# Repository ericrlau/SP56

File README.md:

# SP56
## A ZMK-Powered BLE Keyboard, Inspired By Lily58 & Sofle

> :warning: **This is a partially tested project.** Do not use to create your own copy unless you are willing to debug the hardware and/or firmware. 
## Flash bootloader
Bootloader is pre-loaded on assembled pcbs. If you source your own BLE module you will need to unlock the module and flash the bootloader using the Nordic nrf command line tool. 
```
$ nrfjprog --recover --log 
```
```
$ nrfjprog -f nrf52 --program firmware/bootloader/COBO_nrf52840_bootloader-0.3.2-184-g64ea299_s140_6.1.1.hex
```

------------------------------------
## Upload Firmware 

- See ZMK docs for instructions on setting up ZMK and custimizing firmware.  
	* https://zmkfirmware.dev/docs/user-setup/
	* https://zmkfirmware.dev/docs/customization 
- Default *.uf2 files are pre-loaded on assembled pcbs. If you sourced and assembled your own pcb, you can file deafult pre-built firmware here: 
	- https://github.com/ericrlau/COBO-zmk-config/releases

## PCB
- Source files for pcb are in this repo. They are split into three kicad projects:
	- SP56: main pcb, left and right combined. 
	- SP56_Bottom: Bottom cover PCB. Left and right use the same part so only one copy is created. 
	- SP56_Plate: Switch plate PCB. This must be 1.2mm pcb to allow Kaihl Choc V1 switches to snap in. Left and right use the same part so only one copy is created. 
	- NOTE: KiCad files are created with nightly KiCad 5.99 builds, they are not compatible with current stable release of KiCad 5.
- Bill of materials [BOM Link](https://raw.githack.com/ericrlau/SP56/working/PCB/SP56/bom/ibom.html)
## Build Guide For PCBA
[Build Guide Link](./Build_Guide.md)

## Images

#### Prototype Build

#### Main PCB

#### FR4 Plate

#### Bottom PCB

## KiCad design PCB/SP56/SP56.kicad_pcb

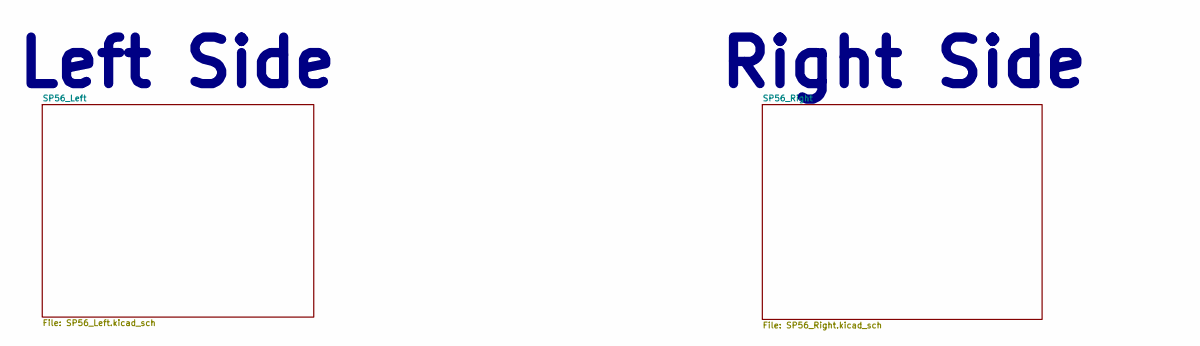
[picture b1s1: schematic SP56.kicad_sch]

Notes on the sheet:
Left Side
Right Side

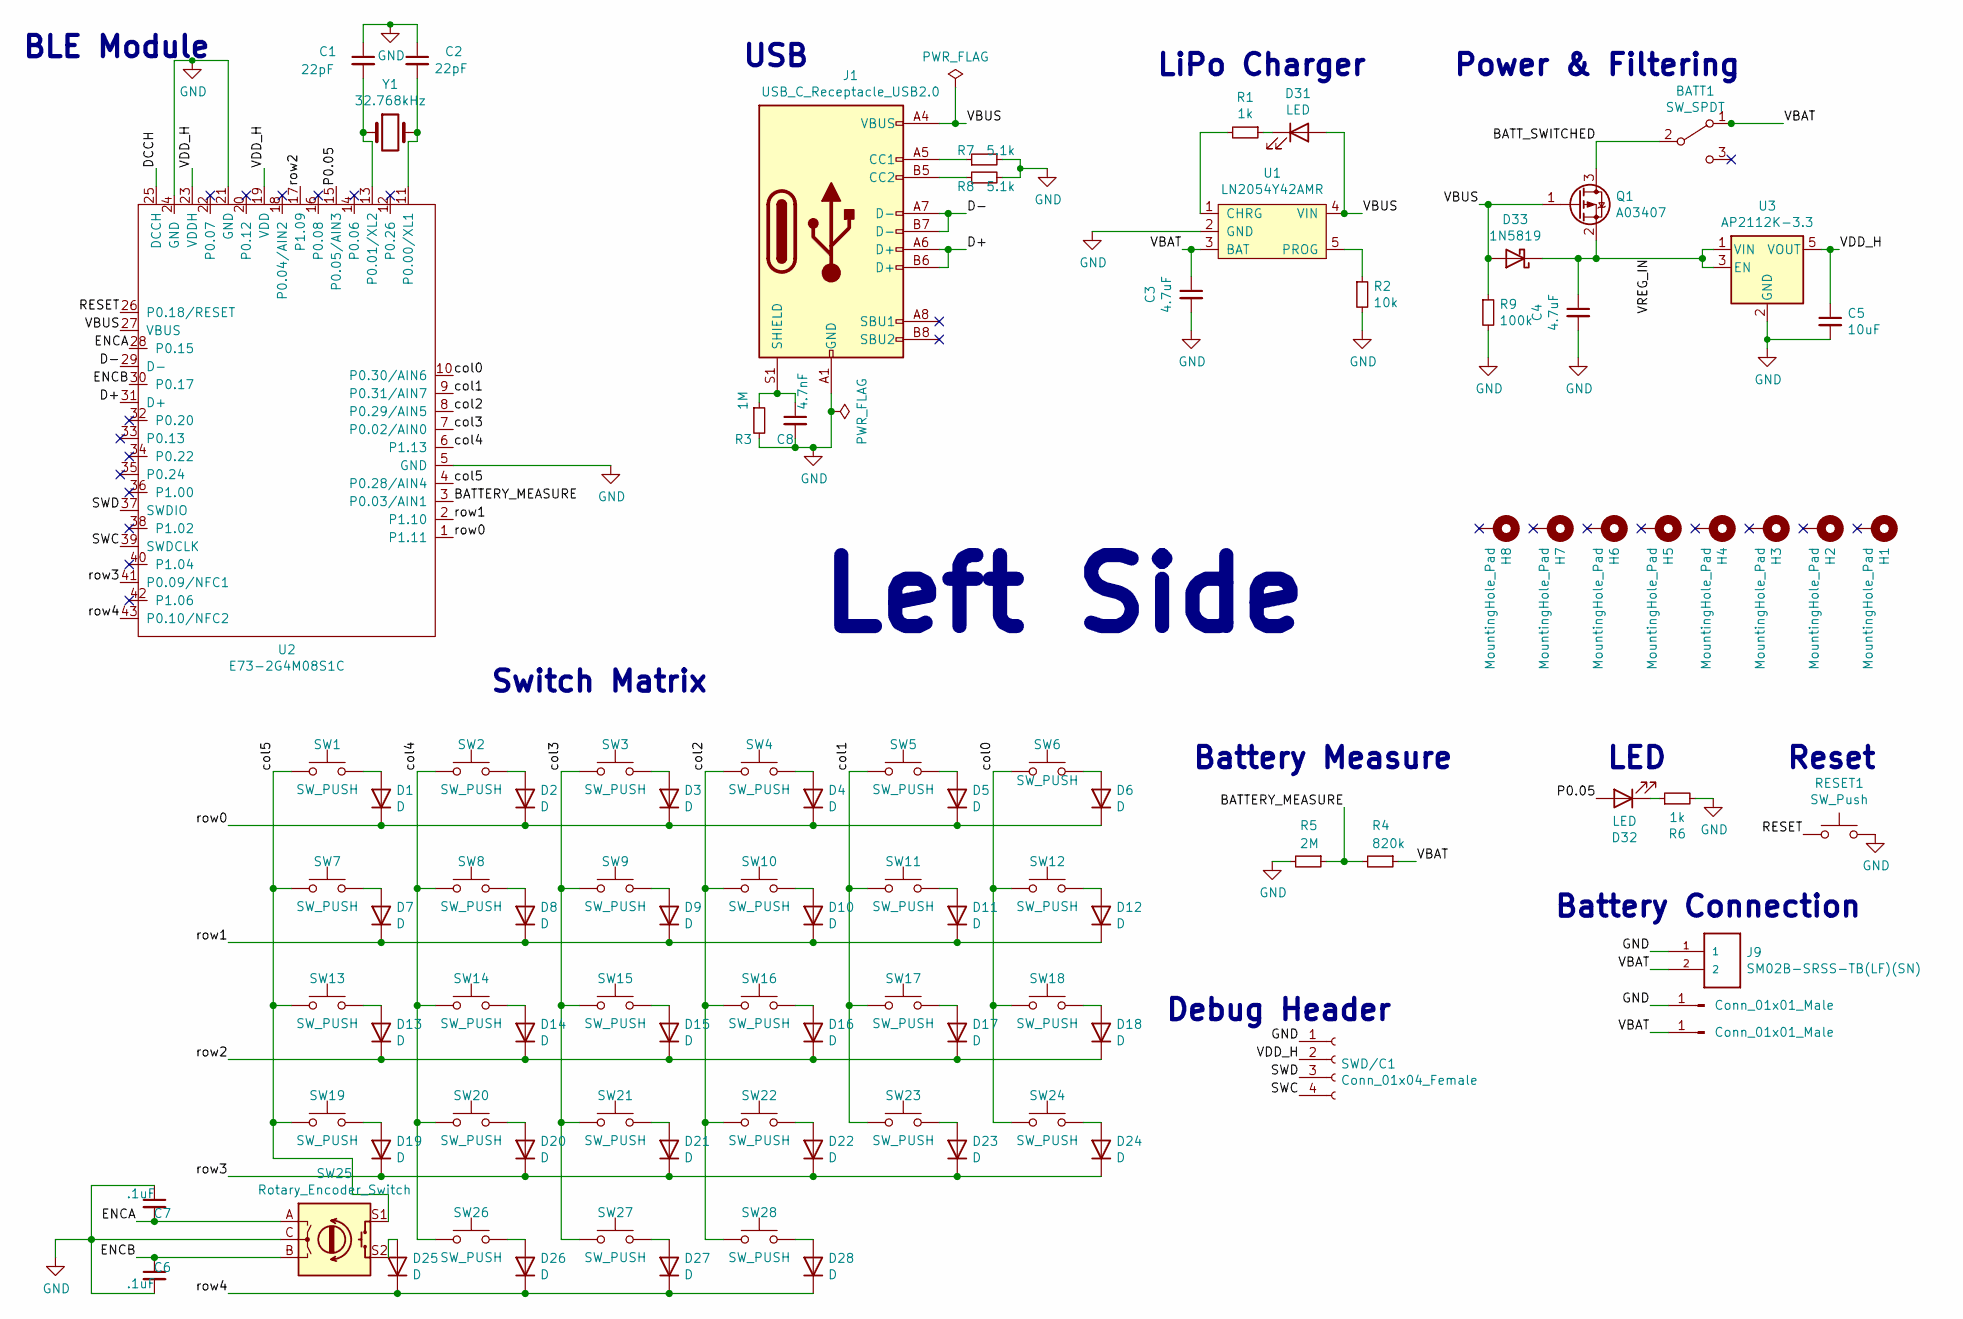
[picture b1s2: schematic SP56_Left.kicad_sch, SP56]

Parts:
BATT1: SW_SPDT; SW-TH_MSK12C02; LCSC_PN C431540
C1, C2: 22pF; C_0603_1608Metric; LCSC_PN C1653
C3, C4: 4.7uF; C_0603_1608Metric; LCSC_PN C19666
C5: 10uF; C_0603_1608Metric; LCSC_PN C87152
C6, C7: .1uF; C_0603_1608Metric
C8: 4.7nF; C_0603_1608Metric
D1, D2, D3, D4, D5, D6, D7, D8, D9, D10, D11, D12, D13, D14, D15, D16, D17, D18, D19, D20, D21, D22, D23, D24, D25, D26, D27, D28: D; D_SOD-123; LCSC_PN C402213
D31, D32: LED; LED_0603_1608Metric
D33: 1N5819; D_SOD-323_HandSoldering; LCSC_PN C489147
H1, H2, H3, H4, H5, H6, H7, H8: MountingHole_Pad; MountingHole_4.3mm_M4
J1: USB_C_Receptacle_USB2.0; USB-C_C168688; LCSC_PN C168688
J2, J3: Conn_01x01_Male; PinSocket_1x01_P1.27mm_Vertical
J9: SM02B-SRSS-TB(LF)(SN); LCSC_PN C160402
Q1: A03407; SOT-23; LCSC_PN C351408
R1, R6: 1k; R_0603_1608Metric; LCSC_PN C22548
R2: 10k; R_0603_1608Metric; LCSC_PN C98220
R3: 1M; R_0603_1608Metric
R4: 820k; R_0603_1608Metric; LCSC_PN C23252
R5: 2M; R_0603_1608Metric; LCSC_PN C177282
R7, R8: 5.1k; R_0603_1608Metric; LCSC_PN C105580
R9: 100k; R_0603_1608Metric; LCSC_PN C14675
RESET1: SW_Push; SW_SPST_B3U-1000P; LCSC_PN C231329
SW1, SW2, SW3, SW4, SW5, SW6, SW7, SW8, SW9, SW10, SW11, SW12, SW13, SW14, SW15, SW16, SW17, SW18, SW19, SW20, SW21, SW22, SW23, SW24, SW27, SW28: SW_PUSH; KailhLowProfile
SW25: Rotary_Encoder_Switch; RotaryEncoder_Alps_EC11E-Switch_Vertical_H20mm
SW26: SW_PUSH; KailhLowProfile_1.5U
SWD/C1: Conn_01x04_Female; PinHeader_1x04_P2.54mm_Vertical
U1: LN2054Y42AMR; SOT-23-5; LCSC_PN C141406
U2: E73-2G4M08S1C; E73-2G4M08S1C-52840_SMD; LCSC_PN C356849
U3: AP2112K-3.3; SOT-23-5; LCSC_PN C51118
Y1: 32.768kHz; Crystal_SMD_MicroCrystal_CM9V-T1A-2Pin_1.6x1.0mm; LCSC_PN C93230

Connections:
/SP56_Left/BATTERY_MEASURE: R4.2, R5.1, U2.3 (P0.03/AIN1)
/SP56_Left/BATT_SWITCHED: BATT1.2 (B), Q1.3 (D)
/SP56_Left/D+: J1.A6 (D+), J1.B6 (D+), U2.31 (D+)
/SP56_Left/D-: J1.A7 (D-), J1.B7 (D-), U2.29 (D-)
/SP56_Left/DCCH: U2.25 (DCCH)
/SP56_Left/ENCA: C7.2, SW25.A, U2.28 (P0.15)
/SP56_Left/ENCB: C6.1, SW25.B, U2.30 (P0.17)
/SP56_Left/P0.05: D32.2 (A), U2.15 (P0.05/AIN3)
/SP56_Left/RESET: RESET1.1, U2.26 (P0.18/RESET)
/SP56_Left/SWC: SWD/C1.4, U2.39 (SWDCLK)
/SP56_Left/SWD: SWD/C1.3, U2.37 (SWDIO)
/SP56_Left/VBAT: BATT1.1 (A), C3.1, J3.1, J9.2, R4.1, U1.3 (BAT)
/SP56_Left/VBUS: D31.2 (A), D33.2 (A), J1.A4 (VBUS), J1.A9 (VBUS), J1.B4 (VBUS), J1.B9 (VBUS), Q1.1 (G), R9.1, U1.4 (VIN), U2.27 (VBUS)
/SP56_Left/VDD_H: C5.1, SWD/C1.2, U2.19 (VDD), U2.23 (VDDH), U3.5 (VOUT)
/SP56_Left/VREG_IN: C4.1, D33.1 (K), Q1.2 (S), U3.1 (VIN), U3.3 (EN)
/SP56_Left/col0: SW6.1, SW12.1, SW18.1, SW24.1, U2.10 (P0.30/AIN6)
/SP56_Left/col1: SW5.1, SW11.1, SW17.1, SW23.1, U2.9 (P0.31/AIN7)
/SP56_Left/col2: SW4.1, SW10.1, SW16.1, SW22.1, SW28.1, U2.8 (P0.29/AIN5)
/SP56_Left/col3: SW3.1, SW9.1, SW15.1, SW21.1, SW27.1, U2.7 (P0.02/AIN0)
/SP56_Left/col4: SW2.1, SW8.1, SW14.1, SW20.1, SW26.1, U2.6 (P1.13)
/SP56_Left/col5: SW1.1, SW7.1, SW13.1, SW19.1, SW25.S1, U2.4 (P0.28/AIN4)
/SP56_Left/row0: D1.1 (K), D2.1 (K), D3.1 (K), D4.1 (K), D5.1 (K), D6.1 (K), U2.1 (P1.11)
/SP56_Left/row1: D7.1 (K), D8.1 (K), D9.1 (K), D10.1 (K), D11.1 (K), D12.1 (K), U2.2 (P1.10)
/SP56_Left/row2: D13.1 (K), D14.1 (K), D15.1 (K), D16.1 (K), D17.1 (K), D18.1 (K), U2.17 (P1.09)
/SP56_Left/row3: D19.1 (K), D20.1 (K), D21.1 (K), D22.1 (K), D23.1 (K), D24.1 (K), U2.41 (P0.09/NFC1)
/SP56_Left/row4: D25.1 (K), D26.1 (K), D27.1 (K), D28.1 (K), U2.43 (P0.10/NFC2)
GND: C1.1, C2.1, C3.2, C4.2, C5.2, C6.2, C7.1, C8.2, J1.A1 (GND), J1.A12 (GND), J1.B1 (GND), J1.B12 (GND), J2.1, J9.1, R2.2, R3.2, R5.2, R6.2, R7.2, R8.2, R9.2, RESET1.2, SW25.C, SWD/C1.1, U1.2 (GND), U2.5 (GND), U2.21 (GND), U2.24 (GND), U3.2 (GND); also elsewhere on the board
unnamed: C1.2, U2.13 (P0.01/XL2), Y1.1
unnamed: C2.2, U2.11 (P0.00/XL1), Y1.2
unnamed: C8.1, J1.S1 (SHIELD), R3.1
unnamed: D1.2 (A), SW1.2
unnamed: D2.2 (A), SW2.2
unnamed: D3.2 (A), SW3.2
unnamed: D4.2 (A), SW4.2
unnamed: D5.2 (A), SW5.2
unnamed: D6.2 (A), SW6.2
unnamed: D7.2 (A), SW7.2
unnamed: D8.2 (A), SW8.2
unnamed: D9.2 (A), SW9.2
unnamed: D10.2 (A), SW10.2
unnamed: D11.2 (A), SW11.2
unnamed: D12.2 (A), SW12.2
unnamed: D13.2 (A), SW13.2
unnamed: D14.2 (A), SW14.2
unnamed: D15.2 (A), SW15.2
unnamed: D16.2 (A), SW16.2
unnamed: D17.2 (A), SW17.2
unnamed: D18.2 (A), SW18.2
unnamed: D19.2 (A), SW19.2
unnamed: D20.2 (A), SW20.2
unnamed: D21.2 (A), SW21.2
unnamed: D22.2 (A), SW22.2
unnamed: D23.2 (A), SW23.2
unnamed: D24.2 (A), SW24.2
unnamed: D25.2 (A), SW25.S2
unnamed: D26.2 (A), SW26.2
unnamed: D27.2 (A), SW27.2
unnamed: D28.2 (A), SW28.2
unnamed: D31.1 (K), R1.1
unnamed: D32.1 (K), R6.1
unnamed: J1.A5 (CC1), R7.1
unnamed: J1.B5 (CC2), R8.1
unnamed: R1.2, U1.1 (CHRG)
unnamed: R2.1, U1.5 (PROG)

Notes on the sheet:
BLE Module
Switch Matrix
USB
Left Side
LiPo Charger
Debug Header
Battery Measure
Power & Filtering
Battery Connection
LED
Reset

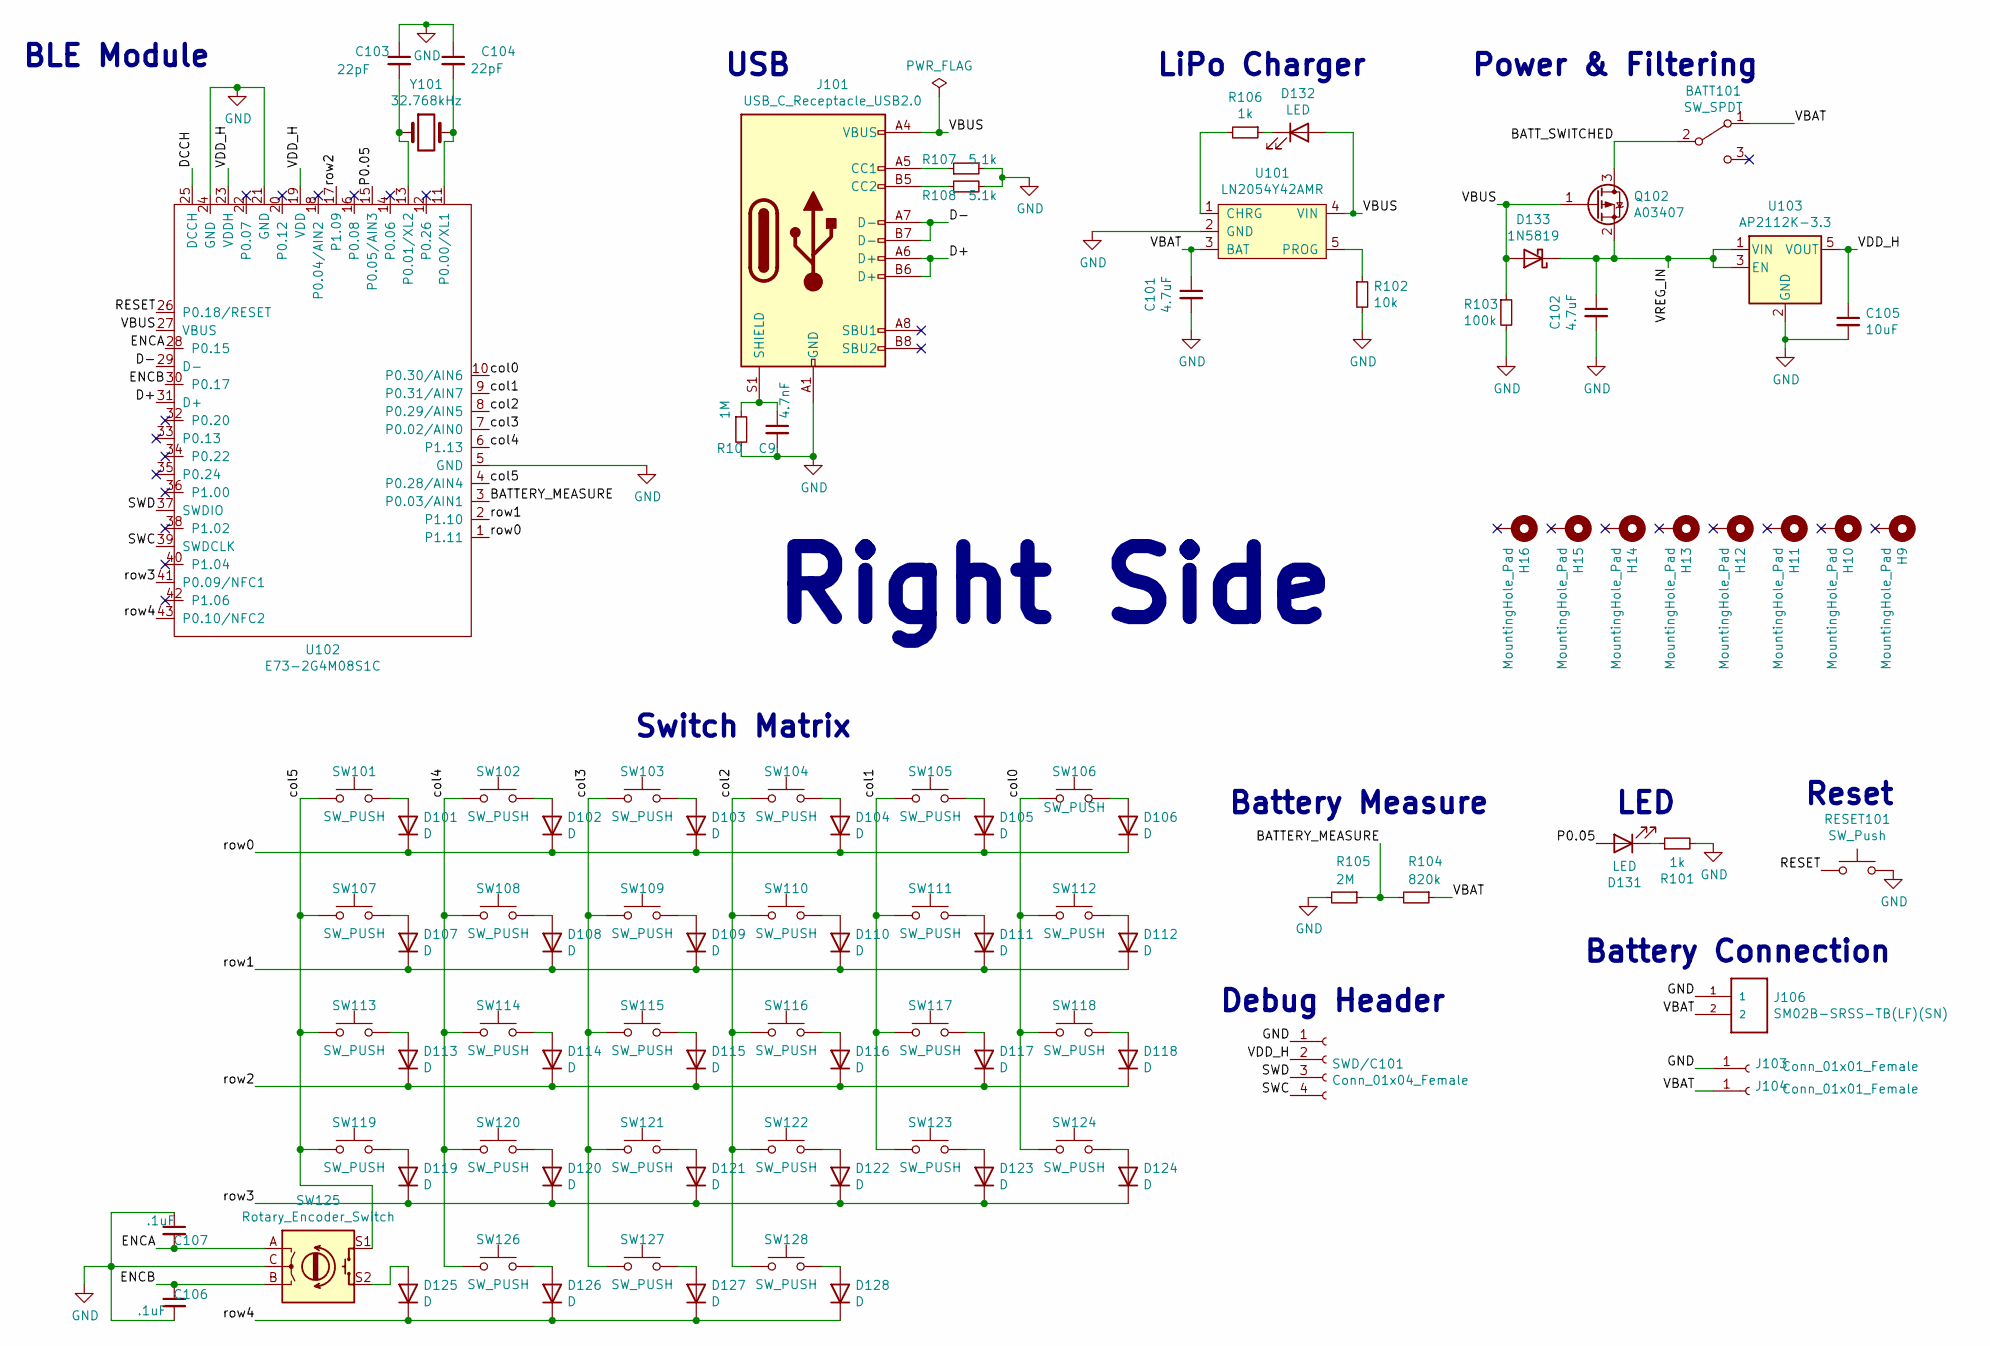
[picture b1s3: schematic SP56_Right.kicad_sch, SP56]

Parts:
BATT101: SW_SPDT; SW-TH_MSK12C02; LCSC_PN C431540
C9: 4.7nF; C_0603_1608Metric
C101, C102: 4.7uF; C_0603_1608Metric; LCSC_PN C19666
C103, C104: 22pF; C_0603_1608Metric; LCSC_PN C1653
C105: 10uF; C_0603_1608Metric; LCSC_PN C326057
C106, C107: .1uF; C_0603_1608Metric
D101, D102, D103, D104, D105, D106, D107, D108, D109, D110, D111, D112, D113, D114, D115, D116, D117, D118, D119, D120, D121, D122, D123, D124, D125, D126, D127, D128: D; D_SOD-123; LCSC_PN C402213
D131, D132: LED; LED_0603_1608Metric
D133: 1N5819; D_SOD-323_HandSoldering; LCSC_PN C489147
H9, H10, H11, H12, H13, H14, H15, H16: MountingHole_Pad; MountingHole_4.3mm_M4
J101: USB_C_Receptacle_USB2.0; USB-C_C168688; LCSC_PN C168688
J103, J104: Conn_01x01_Female; PinSocket_1x01_P1.27mm_Vertical
J106: SM02B-SRSS-TB(LF)(SN); LCSC_PN C160402
Q102: A03407; SOT-23; LCSC_PN C351408
R10: 1M; R_0603_1608Metric
R101, R106: 1k; R_0603_1608Metric; LCSC_PN C22548
R102: 10k; R_0603_1608Metric; LCSC_PN C98220
R103: 100k; R_0603_1608Metric; LCSC_PN C14675
R104: 820k; R_0603_1608Metric; LCSC_PN C23252
R105: 2M; R_0603_1608Metric; LCSC_PN C177282
R107, R108: 5.1k; R_0603_1608Metric; LCSC_PN C105580
RESET101: SW_Push; SW_SPST_B3U-1000P; LCSC_PN C231329
SW101, SW102, SW103, SW104, SW105, SW106, SW107, SW108, SW109, SW110, SW111, SW112, SW113, SW114, SW115, SW116, SW117, SW118, SW119, SW120, SW121, SW122, SW123, SW124, SW127, SW128: SW_PUSH; KailhLowProfile
SW125: Rotary_Encoder_Switch; RotaryEncoder_Alps_EC11E-Switch_Vertical_H20mm
SW126: SW_PUSH; KailhLowProfile_1.5U
SWD/C101: Conn_01x04_Female; PinHeader_1x04_P2.54mm_Vertical
U101: LN2054Y42AMR; SOT-23-5; LCSC_PN C141406
U102: E73-2G4M08S1C; E73-2G4M08S1C-52840_SMD; LCSC_PN C356849
U103: AP2112K-3.3; SOT-23-5; LCSC_PN C51118
Y101: 32.768kHz; Crystal_SMD_MicroCrystal_CM9V-T1A-2Pin_1.6x1.0mm; LCSC_PN C93230

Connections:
/SP56_Right/BATTERY_MEASURE: R104.2, R105.1, U102.3 (P0.03/AIN1)
/SP56_Right/BATT_SWITCHED: BATT101.2 (B), Q102.3 (D)
/SP56_Right/D+: J101.A6 (D+), J101.B6 (D+), U102.31 (D+)
/SP56_Right/D-: J101.A7 (D-), J101.B7 (D-), U102.29 (D-)
/SP56_Right/DCCH: U102.25 (DCCH)
/SP56_Right/ENCA: C107.2, SW125.A, U102.28 (P0.15)
/SP56_Right/ENCB: C106.1, SW125.B, U102.30 (P0.17)
/SP56_Right/P0.05: D131.2 (A), U102.15 (P0.05/AIN3)
/SP56_Right/RESET: RESET101.1, U102.26 (P0.18/RESET)
/SP56_Right/SWC: SWD/C101.4, U102.39 (SWDCLK)
/SP56_Right/SWD: SWD/C101.3, U102.37 (SWDIO)
/SP56_Right/VBAT: BATT101.1 (A), C101.1, J104.1, J106.2, R104.1, U101.3 (BAT)
/SP56_Right/VBUS: D132.2 (A), D133.2 (A), J101.A4 (VBUS), J101.A9 (VBUS), J101.B4 (VBUS), J101.B9 (VBUS), Q102.1 (G), R103.1, U101.4 (VIN), U102.27 (VBUS)
/SP56_Right/VDD_H: C105.1, SWD/C101.2, U102.19 (VDD), U102.23 (VDDH), U103.5 (VOUT)
/SP56_Right/VREG_IN: C102.1, D133.1 (K), Q102.2 (S), U103.1 (VIN), U103.3 (EN)
/SP56_Right/col0: SW106.1, SW112.1, SW118.1, SW124.1, U102.10 (P0.30/AIN6)
/SP56_Right/col1: SW105.1, SW111.1, SW117.1, SW123.1, U102.9 (P0.31/AIN7)
/SP56_Right/col2: SW104.1, SW110.1, SW116.1, SW122.1, SW128.1, U102.8 (P0.29/AIN5)
/SP56_Right/col3: SW103.1, SW109.1, SW115.1, SW121.1, SW127.1, U102.7 (P0.02/AIN0)
/SP56_Right/col4: SW102.1, SW108.1, SW114.1, SW120.1, SW126.1, U102.6 (P1.13)
/SP56_Right/col5: SW101.1, SW107.1, SW113.1, SW119.1, SW125.S1, U102.4 (P0.28/AIN4)
/SP56_Right/row0: D101.1 (K), D102.1 (K), D103.1 (K), D104.1 (K), D105.1 (K), D106.1 (K), U102.1 (P1.11)
/SP56_Right/row1: D107.1 (K), D108.1 (K), D109.1 (K), D110.1 (K), D111.1 (K), D112.1 (K), U102.2 (P1.10)
/SP56_Right/row2: D113.1 (K), D114.1 (K), D115.1 (K), D116.1 (K), D117.1 (K), D118.1 (K), U102.17 (P1.09)
/SP56_Right/row3: D119.1 (K), D120.1 (K), D121.1 (K), D122.1 (K), D123.1 (K), D124.1 (K), U102.41 (P0.09/NFC1)
/SP56_Right/row4: D125.1 (K), D126.1 (K), D127.1 (K), D128.1 (K), U102.43 (P0.10/NFC2)
GND: C9.2, C101.2, C102.2, C103.1, C104.1, C105.2, C106.2, C107.1, J101.A1 (GND), J101.A12 (GND), J101.B1 (GND), J101.B12 (GND), J103.1, J106.1, R10.2, R101.2, R102.2, R103.2, R105.2, R107.2, R108.2, RESET101.2, SW125.C, SWD/C101.1, U101.2 (GND), U102.5 (GND), U102.21 (GND), U102.24 (GND), U103.2 (GND); also elsewhere on the board
unnamed: C9.1, J101.S1 (SHIELD), R10.1
unnamed: C103.2, U102.13 (P0.01/XL2), Y101.1
unnamed: C104.2, U102.11 (P0.00/XL1), Y101.2
unnamed: D101.2 (A), SW101.2
unnamed: D102.2 (A), SW102.2
unnamed: D103.2 (A), SW103.2
unnamed: D104.2 (A), SW104.2
unnamed: D105.2 (A), SW105.2
unnamed: D106.2 (A), SW106.2
unnamed: D107.2 (A), SW107.2
unnamed: D108.2 (A), SW108.2
unnamed: D109.2 (A), SW109.2
unnamed: D110.2 (A), SW110.2
unnamed: D111.2 (A), SW111.2
unnamed: D112.2 (A), SW112.2
unnamed: D113.2 (A), SW113.2
unnamed: D114.2 (A), SW114.2
unnamed: D115.2 (A), SW115.2
unnamed: D116.2 (A), SW116.2
unnamed: D117.2 (A), SW117.2
unnamed: D118.2 (A), SW118.2
unnamed: D119.2 (A), SW119.2
unnamed: D120.2 (A), SW120.2
unnamed: D121.2 (A), SW121.2
unnamed: D122.2 (A), SW122.2
unnamed: D123.2 (A), SW123.2
unnamed: D124.2 (A), SW124.2
unnamed: D125.2 (A), SW125.S2
unnamed: D126.2 (A), SW126.2
unnamed: D127.2 (A), SW127.2
unnamed: D128.2 (A), SW128.2
unnamed: D131.1 (K), R101.1
unnamed: D132.1 (K), R106.1
unnamed: J101.A5 (CC1), R107.1
unnamed: J101.B5 (CC2), R108.1
unnamed: R102.1, U101.5 (PROG)
unnamed: R106.2, U101.1 (CHRG)

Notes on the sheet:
BLE Module
Switch Matrix
USB
Right Side
LiPo Charger
Debug Header
Battery Measure
Power & Filtering
Battery Connection
LED
Reset

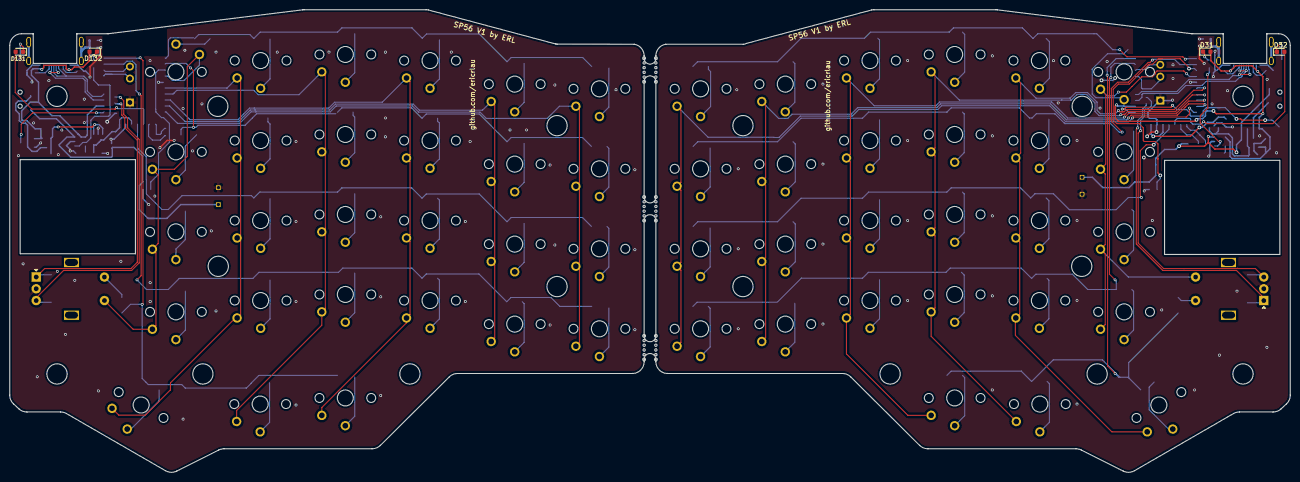
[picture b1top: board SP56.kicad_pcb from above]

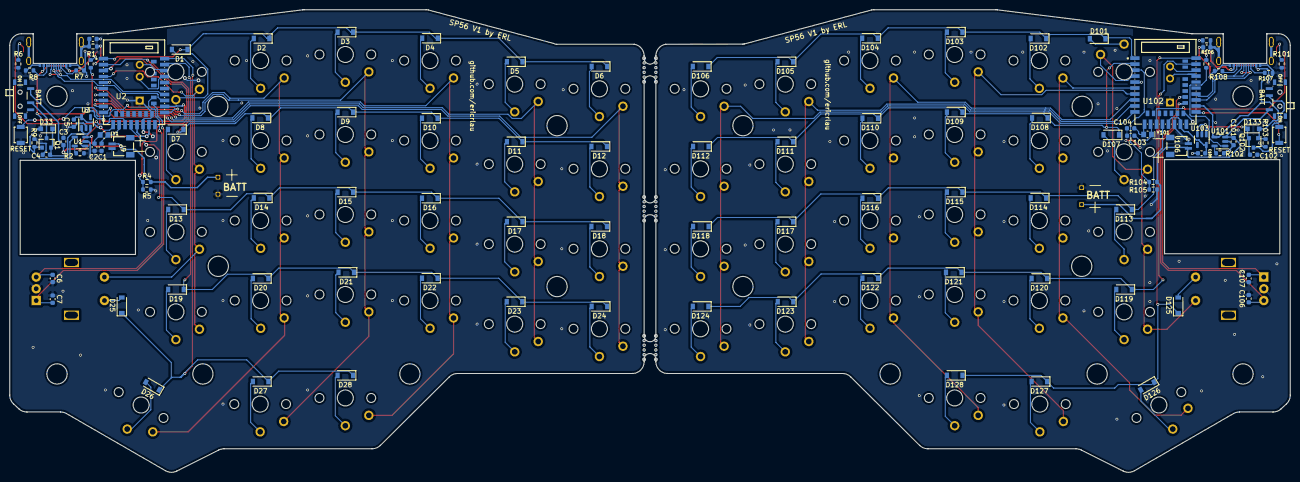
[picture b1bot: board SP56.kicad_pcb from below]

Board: 2 copper layers, 272.1 x 98.3 mm, 192 parts (117 on the bottom side), 125 nets.

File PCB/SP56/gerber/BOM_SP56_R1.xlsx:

Id | Designator | Description | Quantity | Value | Package | LCSC PN | NOTE
1.0 | H14,H10,H8,H13,H11,H12,H15,H7,H16,H9,H1,H3,H6,H5,H2,H4 | Mounting Hole | 16.0 | MountingHole_Pad | MountingHole_4.3mm_M4 | DNI | DNI
2.0 | SW126,SW26 | SW_PUSH | 2.0 | SW_PUSH | KailhLowProfile_1.5U
3.0 | SWD/C1,SWD/C101 | Debug Header | 2.0 | Conn_01x04_Female | PinHeader_1x04_P2.54mm_Vertical
4.0 | SW113,SW2,SW21,SW9,SW1,SW11,SW119,SW106,SW28,SW127,SW123,SW115,SW18,SW27,SW19,S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 | SW_PUSH | 52.0 | SW_PUSH | KailhLowProfile | DNI | DNI
5.0 | J3,J2 | Conn_01x01_Male | 2.0 | Conn_01x01_Male | PinSocket_1x01_P1.27mm_Vertical | DNI | DNI
6.0 | REF**,REF**,REF** | mouseBit_2mm | 3.0 | mouseBit_2mm | mouseBit_2mm | DNI | DNI
7.0 | J104,J103 | Conn_01x01_Female | 2.0 | Conn_01x01_Female | PinSocket_1x01_P1.27mm_Vertical | DNI | DNI
8.0 | D132,D31,D32,D131 | LED | 4.0 | LED | LED_0603_1608Metric | DNI | DNI
9.0 | SW125,SW25 | Rotary_Encoder_Switch | 2.0 | Rotary_Encoder_Switch | RotaryEncoder_Alps_EC11E-Switch_Vertical_H20mm_NoSilkScreen | DNI | DNI
10.0 | D103,D125,D101,D120,D109,D26,D112,D127,D116,D118,D14,D111,D105,D110,D117,D121,D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 | D | 56.0 | 1N4148W | D_SOD-123 | C402213
11.0 | Q1,Q102 | A03407 | 2.0 | A03407 | SOT-23 | C351408
12.0 | R105,R5 | 2M | 2.0 | 2M | R_0603_1608Metric | C177282
13.0 | U101,U1 | LN2054Y42AMR | 2.0 | LN2054Y42AMR | SOT-23-5 | C141406
14.0 | D33,D133 | 1N5819 | 2.0 | 1N5819 | D_SOD-323_HandSoldering | C489147
15.0 | R101,R6,R106,R1 | 1k | 4.0 | 1k | R_0603_1608Metric | C22548
16.0 | C101,C3,C4,C102 | 4.7uF | 4.0 | 4.7uF | C_0603_1608Metric | C19666
17.0 | R103,R9 | 100k | 2.0 | 100k | R_0603_1608Metric | C14675
18.0 | R2,R102 | 10k | 2.0 | 10k | R_0603_1608Metric | C98220
19.0 | Y101,Y1 | 32.768kHz | 2.0 | 32.768kHz | Crystal_SMD_MicroCrystal_CM9V-T1A-2Pin_1.6x1.0mm_HandSoldering | C93230
20.0 | C105,C5 | 10uF | 2.0 | 10uF | C_0603_1608Metric | C326057
21.0 | C2,C103,C104,C1 | 22pF | 4.0 | 22pF | C_0603_1608Metric | C1653
22.0 | J106,J9 | SM02B-SRSS-TB(LF)(SN) | 2.0 | SM02B-SRSS-TB(LF)(SN) | SM02B-SRSS-TB(LF)(SN) | C160402
23.0 | R108,R8,R107,R7 | 5.1k | 4.0 | 5.1k | R_0603_1608Metric | C105580
24.0 | R4,R104 | 820k | 2.0 | 820k | R_0603_1608Metric | C23252
25.0 | BATT101,BATT1 | SW_SPDT | 2.0 | SW_SPDT | SW-TH_MSK12C02 | C431540
26.0 | U102,U2 | E73-2G4M08S1C | 2.0 | E73-2G4M08S1C | E73-2G4M08S1C-52840_SMD | C356849
27.0 | C107,C106,C7,C6 | .1uF | 4.0 | .1uF | C_0603_1608Metric | C14663
28.0 | BattJumper1,BattJumper101 | Jumper_2_Open | 2.0 | Jumper_2_Open | SolderJumper-2_P1.3mm_Open_Pad1.0x1.5mm | DNI | DNI
29.0 | U3,U103 | AP2112K-3.3 | 2.0 | AP2112K-3.3 | SOT-23-5 | C51118
30.0 | RESET101,RESET1 | SW_Push | 2.0 | SW_Push | SW_SPST_B3U-1000P | C231329
31.0 | J101,J1 | USB_C_Receptacle_USB2.0 | 2.0 | USB_C_Receptacle_USB2.0 | USB-C_C168688 | C168688
